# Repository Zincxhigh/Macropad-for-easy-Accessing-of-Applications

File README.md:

# Macropad V4

A 6-key macropad with a rotary encoder and OLED display, built around the **XIAO smd21** and powered by **KMK firmware**.
---

# Features

* 6 keys 
* Rotary encoder for volume control
* Encoder press for mute
* OLED display
* Shows **volume bar when Changing volume**
* Shows **date and time when it is doing nothing**
* **KMK firmware**

---
## BOM

* 6 × switches
* 5 × diode_SMD
* 2 x diode_THT
* 1 × EC11 rotary encoder
* 1 × OLED Conn_01x04

---
| Component             | Function         | Microcontroller Pin |
| -------------------- | ---------------- | ------------------ |
| Key 1                 | Macro key input  | D0                  |
| Key 2                 | Macro key input  | D1                  |
| Key 3                 | Macro key input  | D2                  |
| Key 4                 | Macro key input  | D3                  |
| Key 5                 | Macro key input  | D4                  |
| Key 6                 | Macro key input  | D5                  |
| Rotary Encoder A      | Encoder signal A | D6                  |
| Rotary Encoder B      | Encoder signal B | D7                  |
| Rotary Encoder Button | Push switch      | D8                  |
| OLED SDA              | Conn_01x04 Data  | SDA                 |
| OLED SCL              | Conn_01x04 Clock | SCL                 |
| VCC                   | Power            | 3.3V                |
| GND                   | Ground           | GND                 |

# Layout for board

| COL0   | COL1    | COL2            |
| ------ | ------- | --------------- |
| KiCad  | Discord | Next Desktop    |
| VSCode | Browser | Current Desktop |

Rotary Encoder:

* Rotate → Volume up/down
* Press → Mute

---

# Firmware

Firmware is written using **KMK**.
I will do debugging when parts arrive
Thanks to hackclub

# refrences

## Schematic

## PCB

## #D model Board

# Structure

```
macropad/
│
├── firmware/
│   └── code.py
│
├── CAD/
│   ├── schematic.kicad_sch
│   ├── pcb.kicad_pcb
│   └── macropad.step
│
├── Production/
│   ├── Top.STEP
│   ├── Bottom.STEP
│   └── gerber.zip
│ 
├── PCB/
│   ├── macropad.kicad_sch
│   ├── macropad.kicad_pcb
│   └── macropad.kicad_pro
│
└── README.md
```

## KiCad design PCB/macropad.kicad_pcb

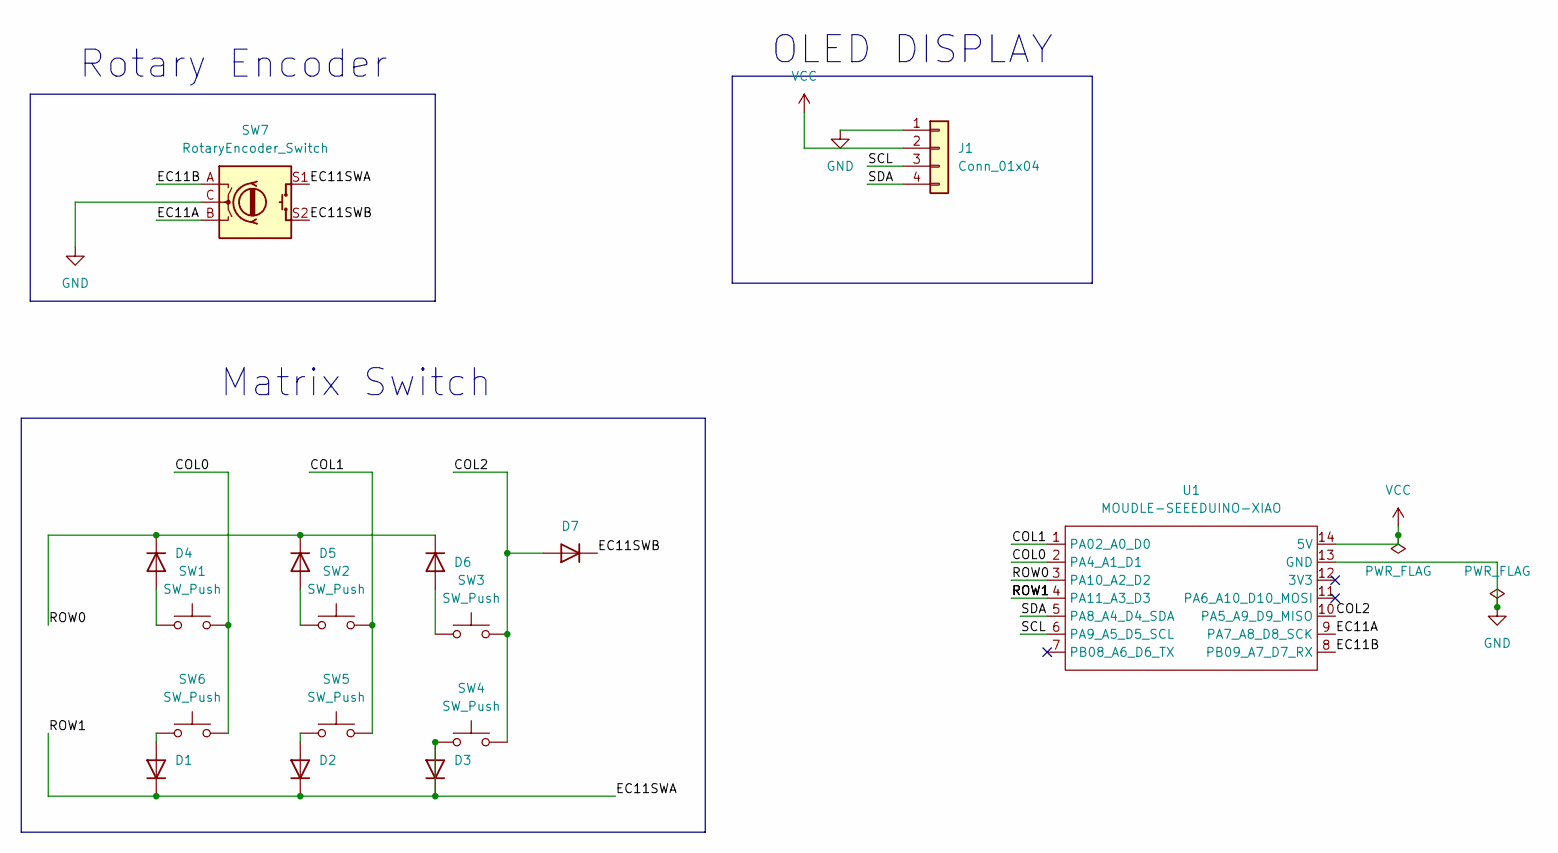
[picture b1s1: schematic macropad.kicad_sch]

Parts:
D1, D3: 1N4148; D_DO-35_SOD27_P7.62mm_Horizontal
D2, D4, D5, D6, D7: 1N4148WT; D_DO-35_SOD27_P7.62mm_Horizontal
J1: Conn_01x04; OLED_0.91_128x32
SW1, SW2, SW3, SW4, SW5, SW6: SW_Push; SW_Cherry_MX_1.00u_PCB
SW7: RotaryEncoder_Switch; RotaryEncoder_Alps_EC11E-Switch_Vertical_H20mm
U1: MOUDLE-SEEEDUINO-XIAO; XIAO-Generic-Hybrid-14P-2.54-21X17.8MM

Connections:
/COL0: SW1.2, SW6.2, U1.2 (PA4_A1_D1)
/COL1: SW2.2, SW5.2, U1.1 (PA02_A0_D0)
/COL2: D7.2 (A), SW3.2, SW4.2, U1.10 (PA5_A9_D9_MISO)
/EC11A: SW7.B, U1.9 (PA7_A8_D8_SCK)
/EC11B: SW7.A, U1.8 (PB09_A7_D7_RX)
/EC11SWA: D1.1 (K), D2.1 (K), D3.1 (K), D3.2 (A), SW4.1, SW7.S1, U1.4 (PA11_A3_D3)
/EC11SWB: D7.1 (K), SW7.S2
/ROW0: D4.1 (K), D5.1 (K), D6.1 (K), U1.3 (PA10_A2_D2)
/SCL: J1.3, U1.6 (PA9_A5_D5_SCL)
/SDA: J1.4, U1.5 (PA8_A4_D4_SDA)
GND: J1.1, SW7.C, U1.13 (GND)
unnamed: D1.2 (A), SW6.1
unnamed: D2.2 (A), SW5.1
unnamed: D4.2 (A), SW1.1
unnamed: D5.2 (A), SW2.1
unnamed: D6.2 (A), SW3.1
VCC: J1.2, U1.14 (5V)

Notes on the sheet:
OLED DISPLAY
Matrix Switch
Rotary Encoder

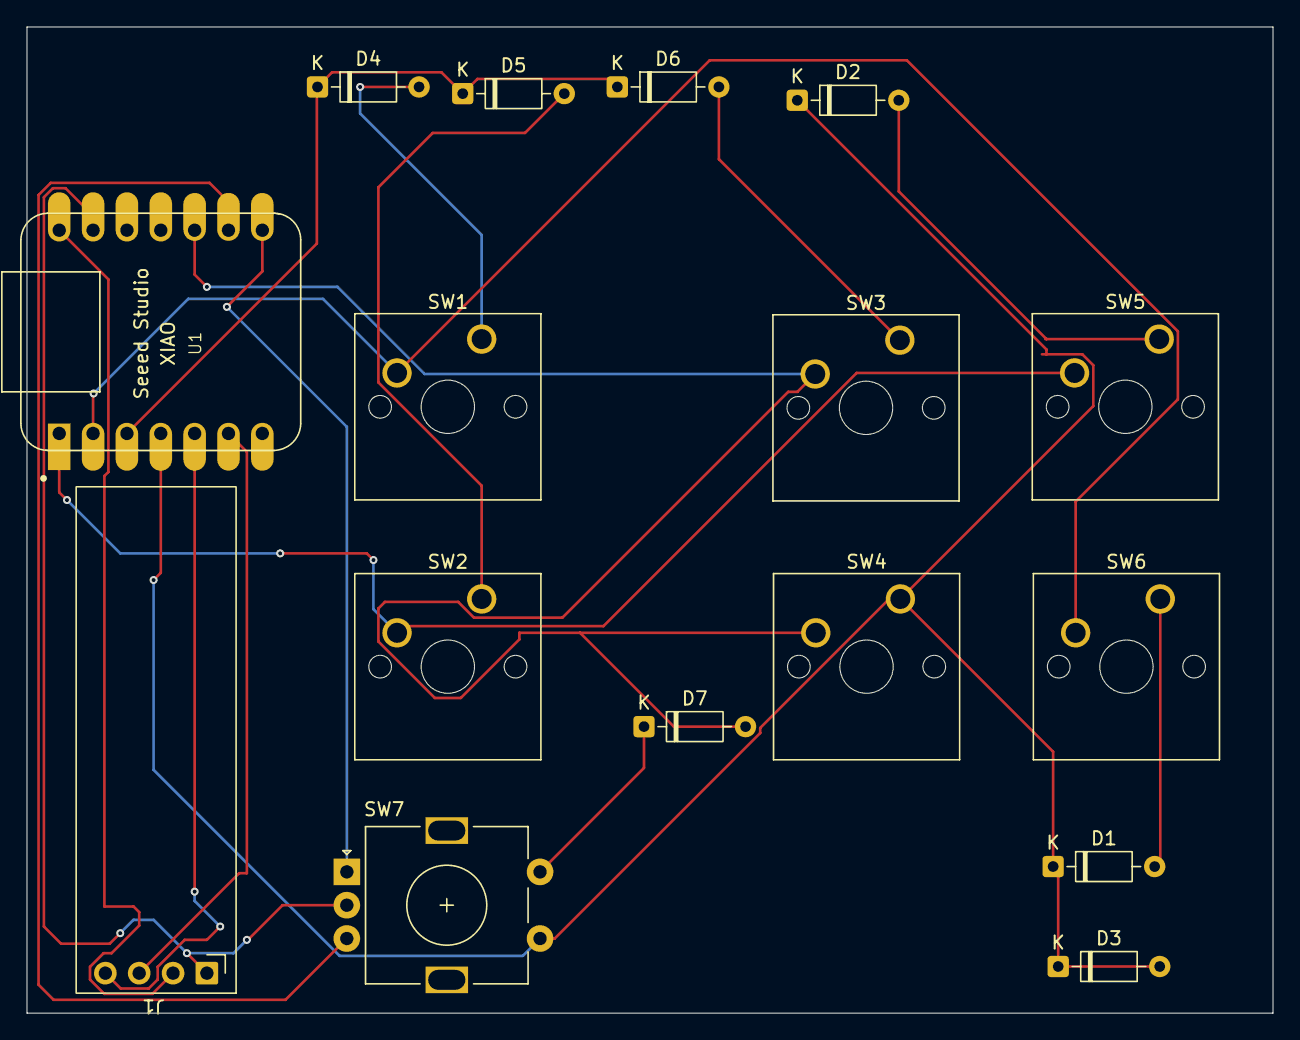
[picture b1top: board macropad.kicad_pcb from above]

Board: 2 copper layers, 93.5 x 74.0 mm, 16 parts (0 on the bottom side), 17 nets.

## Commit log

2026-02-27 Enhance README with detailed macropad description
    Expanded description of the macropad's features and components.
2026-03-12 Clarify feature descriptions in README
    Updated feature descriptions for clarity.
2026-03-12 old pcb
2026-03-14 Fix image source path in PCB section
2026-03-14 Rename Snipaste_2026-03-14_21-36-08-1.png to PCB.png
